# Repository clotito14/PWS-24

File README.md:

# Linear Power Supply Project
## Chase Lotito - Lotito Labs - 06.16.2024

The following project is to learn more about circuit design and PCB design via making a linear power supply.

During this project, I used online resources for the structure of the circuit and KiCAD for schematics and the PCB.

### Design Requirements:
* Input: +120VAC 60Hz connects from mains.
* Output: Variable 0-20VDC @ 3A max.

### Circuit Structure:

120VAC INPUT -> STEP-DOWN TRANSFORMER -> 16VAC -> FULL-BRIDGE RECTIFIER -> FILTER CAPACITOR -> VOLTAGE REGULATOR -> 0-20VDC OUTPUT

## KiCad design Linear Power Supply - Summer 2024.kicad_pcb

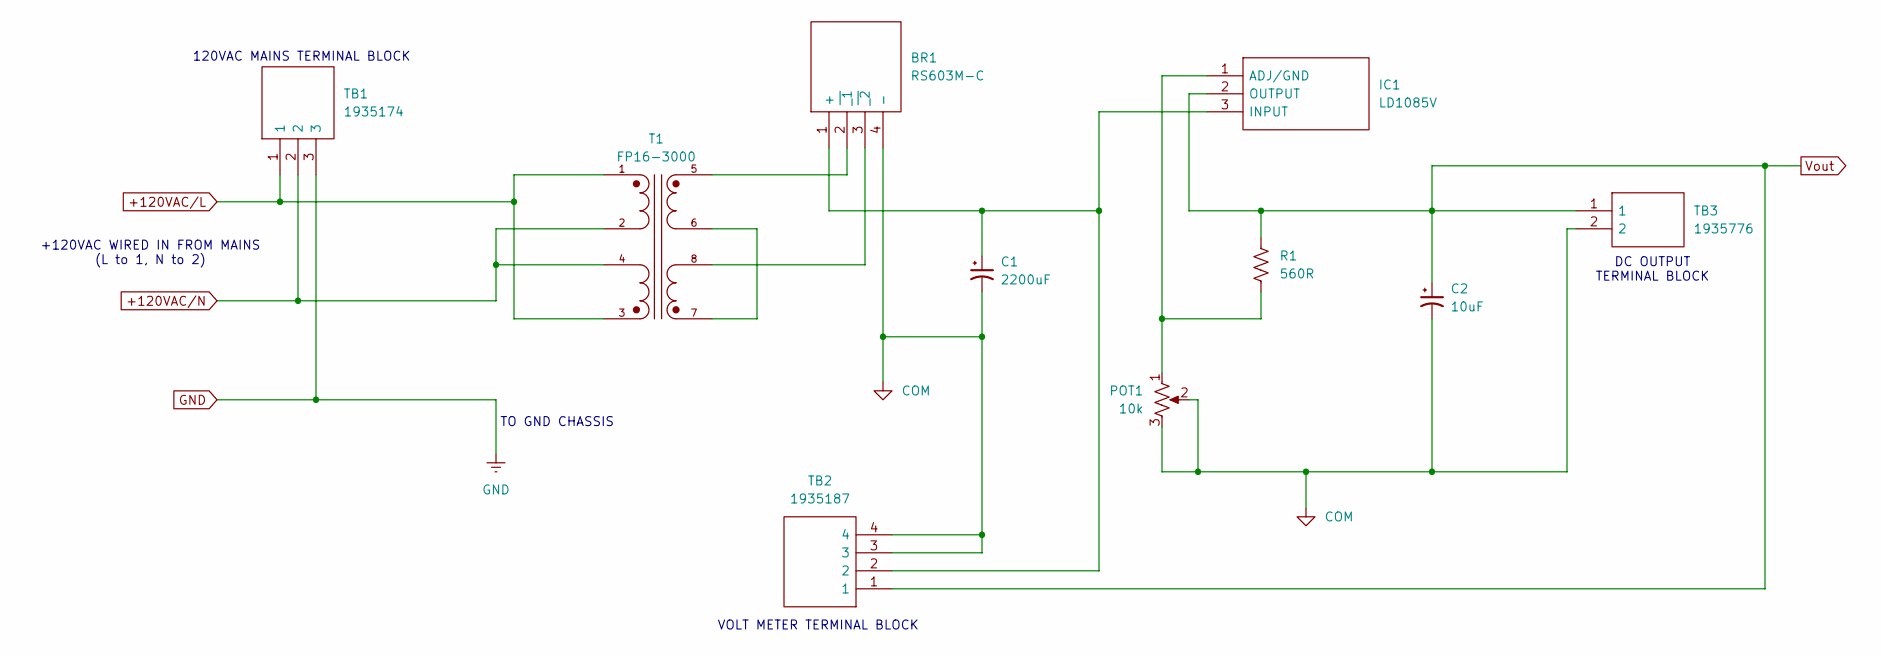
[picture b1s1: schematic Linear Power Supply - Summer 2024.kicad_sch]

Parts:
BR1: RS603M-C; RS603MC; Manufacturer_Part_Number RS603M-C; Mouser Part Number 583-RS603M
C1: 2200uF; 228SAK050M
C2: 10uF; Small Electrolytic Capacitor
IC1: LD1085V; TO255P460X1020X2008-3P; Manufacturer_Part_Number LD1085V; Mouser Part Number 511-LD1085V
POT1: 10k; 1935174
R1: 560R; R_Axial_DIN0204_L3.6mm_D1.6mm_P7.62mm_Horizontal
T1: FP16-3000; XFMR_FP16-3000
TB1: 1935174; Manufacturer_Part_Number 1935174; Mouser Part Number 651-1935174
TB2: 1935187; Manufacturer_Part_Number 1935187; Mouser Part Number 651-1935187
TB3: 1935776; Manufacturer_Part_Number 1935776; Mouser Part Number 651-1935776

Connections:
+120VAC/L: T1.1, T1.3, TB1.1
+120VAC/N: T1.2, T1.4, TB1.2
COM: BR1.4 (-), C1.2, C2.2, POT1.2, POT1.3, TB2.3, TB2.4, TB3.2
GND: TB1.3
unnamed: BR1.1 (+), C1.1, IC1.3 (INPUT), TB2.2
unnamed: BR1.2 (~_1), T1.5
unnamed: BR1.3 (~_2), T1.8
unnamed: IC1.1 (ADJ/GND), POT1.1, R1.2
unnamed: T1.6, T1.7
Vout: C2.1, IC1.2 (OUTPUT), R1.1, TB2.1, TB3.1

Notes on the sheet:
DC OUTPUT TERMINAL BLOCK
120VAC MAINS TERMINAL BLOCK
VOLT METER TERMINAL BLOCK
+120VAC WIRED IN FROM MAINS (L to 1, N to 2)
TO GND CHASSIS

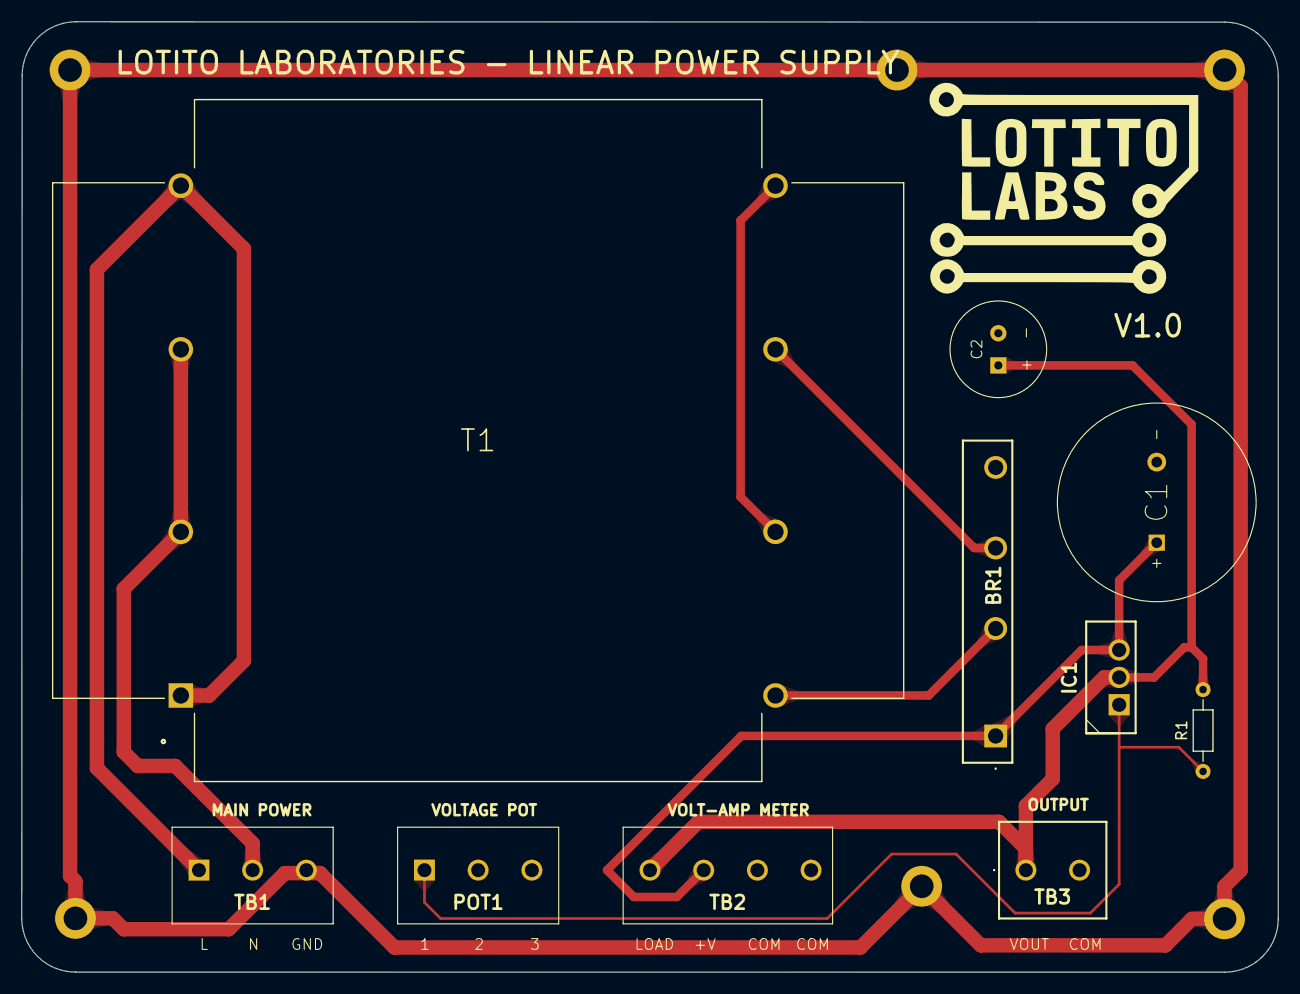
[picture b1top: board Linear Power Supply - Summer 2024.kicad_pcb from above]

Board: 2 copper layers, 117.0 x 88.5 mm, 10 parts (0 on the bottom side), 9 nets.

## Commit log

2024-06-16 First Commit.
2024-06-16 Added README.
2024-06-17 Big push on the PCB layout. I think ready to send to JLC or OSH...
2024-07-03 Finished PCB design...
2024-07-13 Project finished.
2024-08-13 Last updates to .zip
